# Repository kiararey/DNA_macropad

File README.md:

# DNA_macropad
For hardcore DNA writing 😤
Get rid of all pesky useless letters on your keyboard and upgrade your DNA/RNA design experience

I'm following a combination of guides to make this:

ai03's guide: https://wiki.ai03.com/books/pcb-design/page/pcb-guide-part-1---preparations

masterzen's guide: https://www.masterzen.fr/2020/05/03/designing-a-keyboard-part-1/

zycrah's guide: https://guide.zykrah.me

kokaku's PCB notes: https://docs.google.com/document/u/0/d/1xsjb1sf3pxFw8bXC4gNhWsFhWNOthMoyz6RiJc1UtVI/mobilebasic

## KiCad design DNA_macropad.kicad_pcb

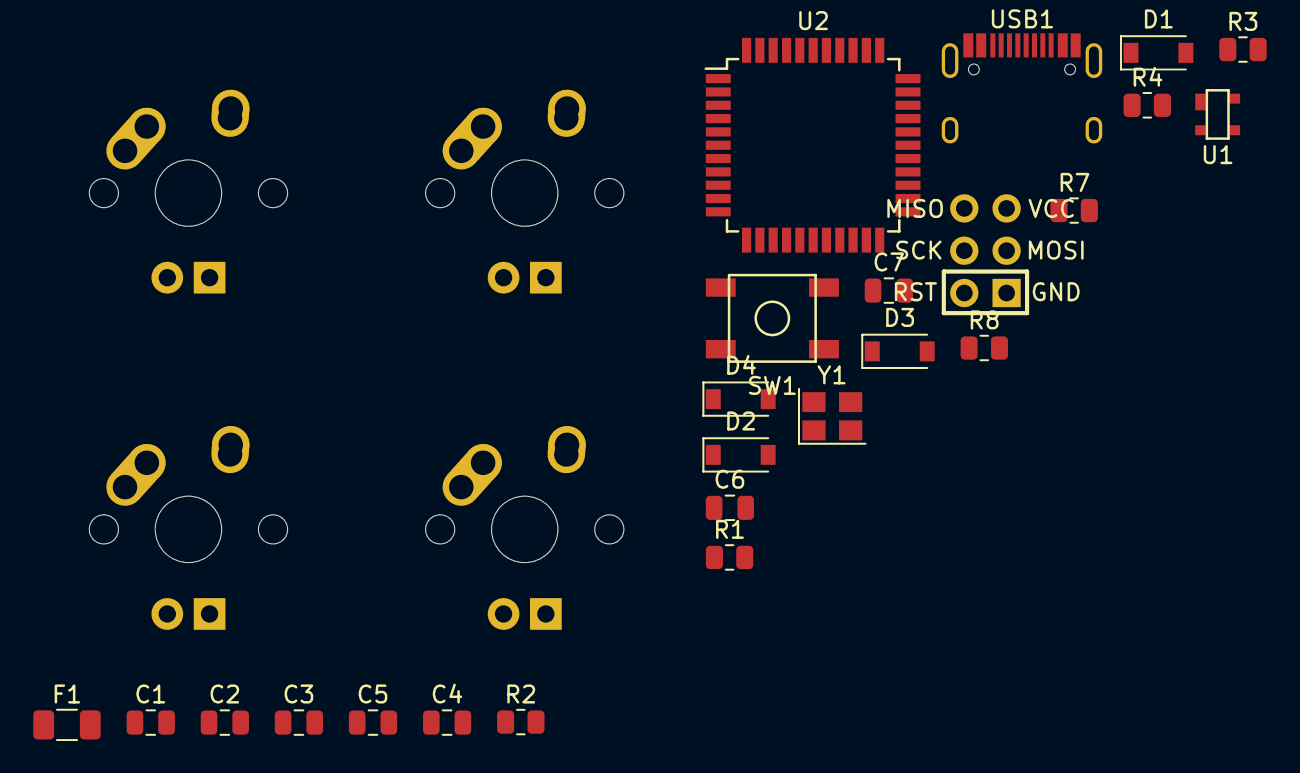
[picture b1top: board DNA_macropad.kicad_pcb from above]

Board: 2 copper layers, 28 parts (0 on the bottom side), 24 nets, no tracks yet.

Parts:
C1, C2: 22 pF; C_0805_2012Metric
C3: 1 uF; C_0805_2012Metric
C4, C5, C6: 0.1 μF; C_0805_2012Metric
C7: 10 μF; C_0805_2012Metric
D1, D2, D3, D4: SOD-123; D_SOD-123
F1: 500 mA; Fuse_1206_3216Metric
J1: AVR-ISP-6; Reset_Pretty-Mask
MX1: A; MX-1U
MX2: C; MX-1U
MX3: T/U; MX-1U
MX4: G; MX-1U
R1, R2: 5.1 kΩ; R_0805_2012Metric
R3, R4: 22 Ω; R_0805_2012Metric
R7, R8: 10 kΩ; R_0805_2012Metric
SW1: SW_Push; SKQG-1155865
U1: PRTR5V0U2X; SOT143B
U2: ATmega32U4-A; TQFP-44_10x10mm_P0.8mm
USB1: HRO-TYPE-C-31-M-12
Y1: 16 MHz; Crystal_SMD_3225-4Pin_3.2x2.5mm

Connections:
+5V: C4.1, C5.1, C6.1, C7.1, F1.2, J1.2 (VCC), R7.1, U2.2 (UVCC), U2.7 (VBUS), U2.14 (VCC), U2.24 (AVCC), U2.34 (VCC), U2.44 (AVCC)
/COL0: MX1.1 (COL), MX2.1 (COL), U2.29 (PB5)
/COL1: MX3.1 (COL), MX4.1 (COL), U2.28 (PB4)
/D+: R4.1, U2.4 (D+)
/D-: R3.2, U2.3 (D-)
/MISI: J1.4 (MOSI), U2.11 (PB3)
/MISO: J1.1 (MISO), U2.10 (PB2)
/RESET: J1.5 (~RST), R7.2, SW1.2, U2.13 (~RESET)
/ROW0: D1.1 (K), D3.1 (K), U2.27 (PD7)
/ROW1: D2.1 (K), D4.1 (K), U2.30 (PB6)
/SCK: J1.3 (SCK), U2.9 (PB1)
GND: C1.1, C2.1, C3.2, C4.2, C5.2, C6.2, C7.2, J1.6 (GND), R1.2, R2.2, R8.2, SW1.1, U1.1 (GND), U2.5 (UGND), U2.15 (GND), U2.23 (GND), U2.35 (GND), U2.43 (GND), USB1.1 (GND), USB1.12 (GND), USB1.13 (SHIELD), Y1.2, Y1.4
unnamed: C1.2, U2.17 (XTAL1), Y1.1
unnamed: C2.2, U2.16 (XTAL2), Y1.3
unnamed: C3.1, U2.6 (UCAP)
unnamed: D1.2 (A), MX1.2 (ROW)
unnamed: D2.2 (A), MX2.2 (ROW)
unnamed: D3.2 (A), MX3.2 (ROW)
unnamed: D4.2 (A), MX4.2 (ROW)
unnamed: R1.1, USB1.10 (CC2)
unnamed: R2.1, R4.2, U1.2 (IO1), USB1.4 (CC1), USB1.6 (DP1), USB1.8 (DP2)
unnamed: R3.1, U1.3 (IO2), USB1.5 (DN2), USB1.7 (DN1)
unnamed: R8.1, U2.33 (~HWB/PE2)
VCC: F1.1, U1.4 (VCC), USB1.2 (VBUS), USB1.11 (VBUS)

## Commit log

2022-10-09 Adding parts libraries
2022-10-09 Added part libraries
2022-10-09 oops forgot this libary
2022-10-09 Moving files
2022-10-09 Finished electrical schematic
2022-10-09 Started PCB design
